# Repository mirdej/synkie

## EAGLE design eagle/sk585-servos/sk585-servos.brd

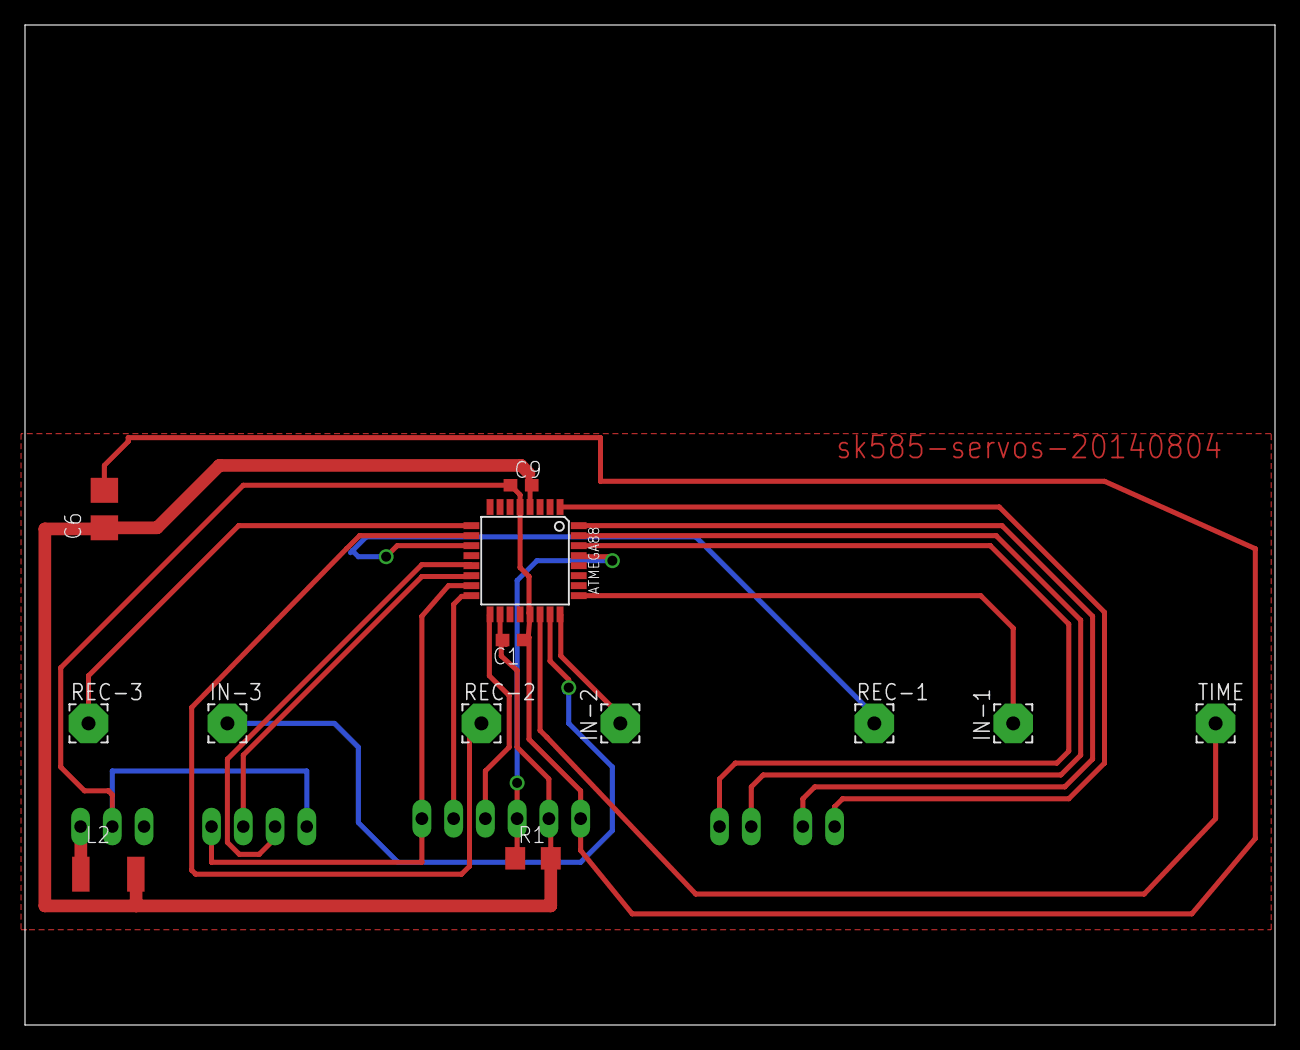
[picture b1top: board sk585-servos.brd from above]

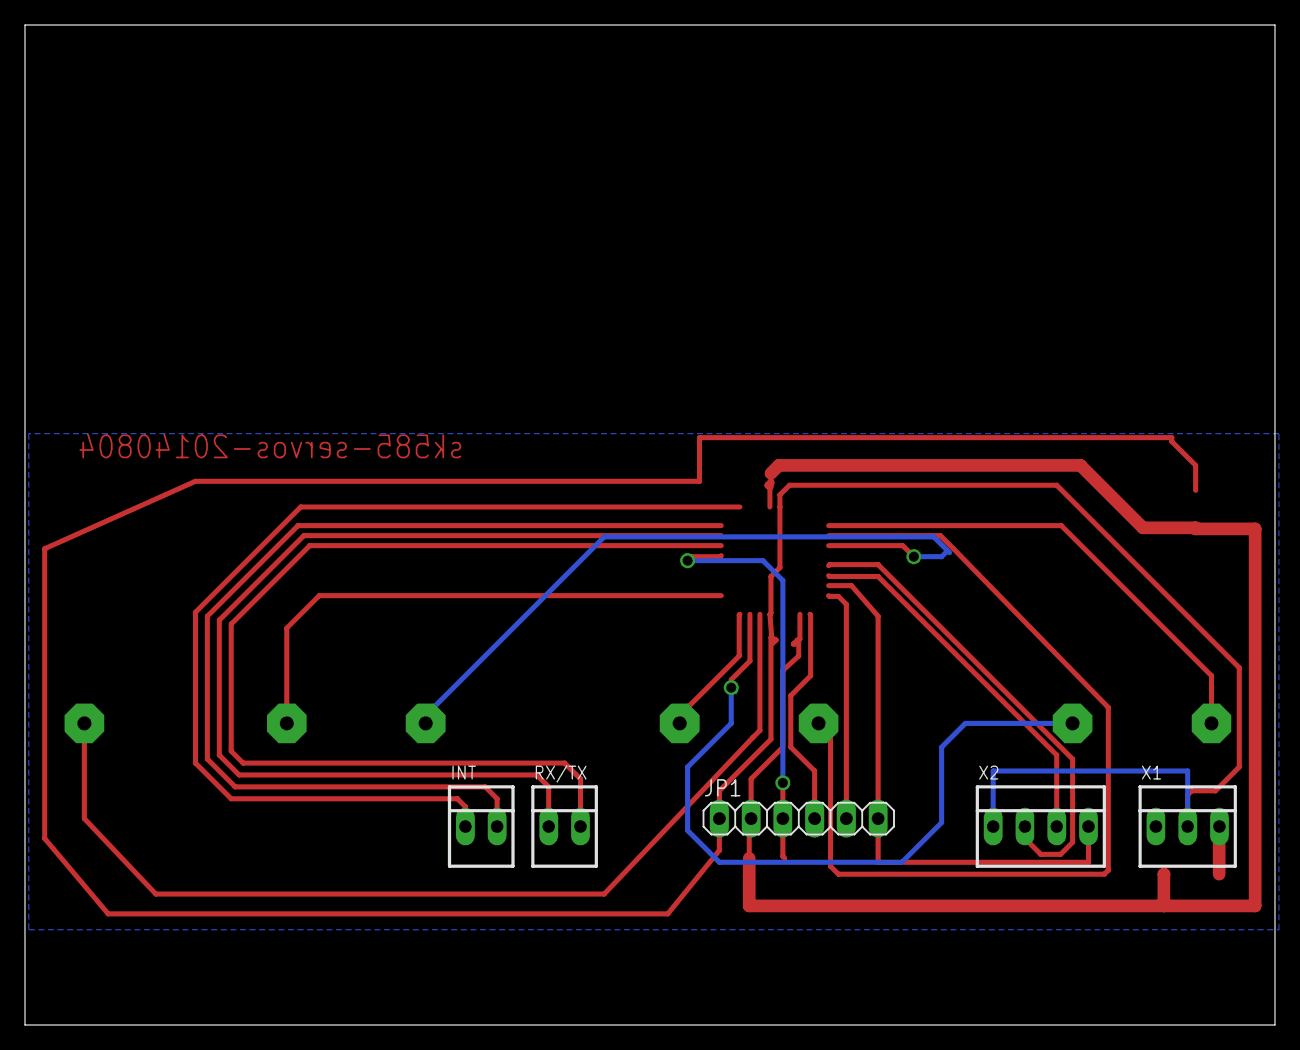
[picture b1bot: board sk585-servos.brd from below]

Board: 2 copper layers, 100.0 x 80.0 mm, 18 parts (5 on the bottom side), 20 nets.

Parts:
ATMEGA88: ATMEGA88; TQFP32-08
C1, C9: C0603
C6: 10u; CT3528
IN-1, IN-2, IN-3: 3,17/1,1
INT: 22-23-2021
JP1: 1X06
L2: L5038P
R1: R1206
REC-1, REC-2, REC-3: 3,17/1,1
RX/TX: 22-23-2021
TIME: 3,17/1,1
X1: 22-23-2031
X2: 22-23-2041

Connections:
+5V: ATMEGA88.4, ATMEGA88.18, C1.2, C6.+, C9.2, JP1.2, L2.2, R1.2
GND: ATMEGA88.5, ATMEGA88.21, C1.1, C6.-, C9.1, JP1.1, X1.2, X2.1
unnamed: ATMEGA88.29, JP1.3, R1.1
unnamed: ATMEGA88.17, JP1.4
unnamed: ATMEGA88.16, JP1.5
unnamed: ATMEGA88.23, IN-3.1
unnamed: ATMEGA88.24, IN-2.1
unnamed: ATMEGA88.25, IN-1.1
unnamed: ATMEGA88.22, TIME.1
unnamed: ATMEGA88.31, RX/TX.1
unnamed: ATMEGA88.11, REC-1.1
unnamed: ATMEGA88.10, REC-2.1
unnamed: L2.1, X1.3
unnamed: ATMEGA88.9, REC-3.1
unnamed: ATMEGA88.30, RX/TX.2
unnamed: ATMEGA88.1, INT.1
unnamed: ATMEGA88.13, X2.2
unnamed: ATMEGA88.32, INT.2
unnamed: ATMEGA88.14, X2.3
unnamed: ATMEGA88.15, JP1.6, X2.4

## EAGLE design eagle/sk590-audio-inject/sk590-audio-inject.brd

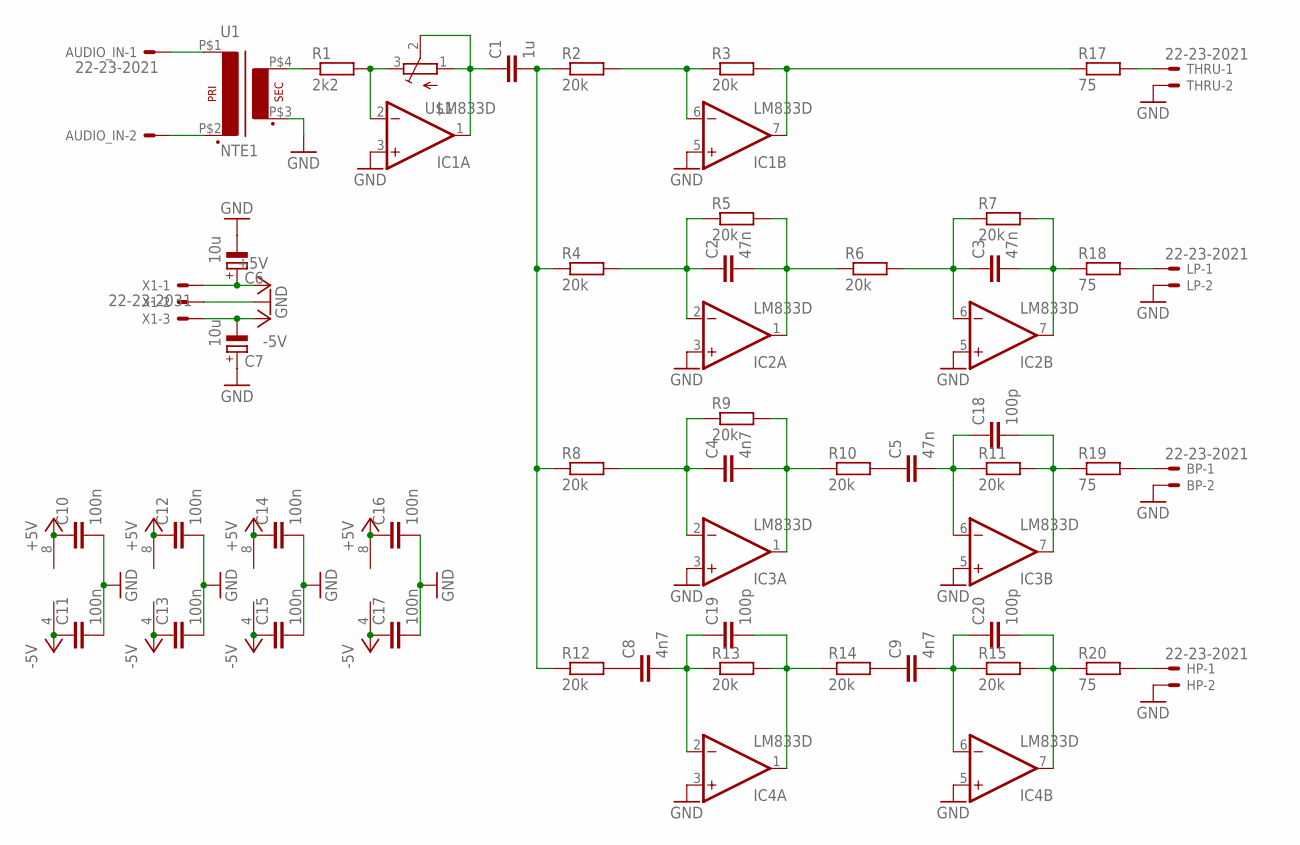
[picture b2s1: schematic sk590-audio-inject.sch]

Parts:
AUDIO_IN: 22-23-2021
BP: 22-23-2021
C1: 1u; C1206
C2, C3, C5: 47n; C1206
C4, C8, C9: 4n7; C1206
C6, C7: 10u; CT3528
C10, C11, C12, C13, C14, C15, C16, C17: 100n; C1206
C18, C19, C20: 100p; C1206
HP: 22-23-2021
IC1, IC2, IC3, IC4: LM833D; SO08
LP: 22-23-2021
R1: 2k2; R1206
R2, R3, R4, R5, R6, R7, R8, R9, R10, R11, R12, R13, R14, R15: 20k; R1206
R17, R18, R19, R20: 75; R1206
THRU: 22-23-2021
U1: NTE1; AUDIOTRAFO
U$1: ALPS_RK09K111_HOHNE-FüSSE; ALPS_RK09K111
X1: 22-23-2031

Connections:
+5V: C6.+, C10.1, C12.1, C14.1, C16.1, IC1.8 (V+), IC2.8 (V+), IC3.8 (V+), IC4.8 (V+), X1.1
-5V: C7.-, C11.1, C13.1, C15.1, C17.1, IC1.4 (V-), IC2.4 (V-), IC3.4 (V-), IC4.4 (V-), X1.3
GND: BP.2, C6.-, C7.+, C10.2, C11.2, C12.2, C13.2, C14.2, C15.2, C16.2, C17.2, HP.2, IC1.3 (+IN), IC1.5 (+IN), IC2.3 (+IN), IC2.5 (+IN), IC3.3 (+IN), IC3.5 (+IN), IC4.3 (+IN), IC4.5 (+IN), LP.2, THRU.2, U1.P$3 (S3), X1.2
unnamed: R1.1, U1.P$4 (S4)
unnamed: AUDIO_IN.1, U1.P$1 (P1)
unnamed: AUDIO_IN.2, U1.P$2 (P2)
unnamed: IC1.2 (-IN), R1.2, U$1.3 (E)
unnamed: C1.1, IC1.1 (OUT), U$1.1 (S), U$1.2 (W)
unnamed: C1.2, R2.1, R4.1, R8.1, R12.1
unnamed: IC1.6 (-IN), R2.2, R3.1
unnamed: IC1.7 (OUT), R3.2, R17.1
unnamed: C2.1, IC2.2 (-IN), R4.2, R5.1
unnamed: C2.2, IC2.1 (OUT), R5.2, R6.1
unnamed: C3.1, IC2.6 (-IN), R6.2, R7.1
unnamed: C3.2, IC2.7 (OUT), R7.2, R18.1
unnamed: C5.1, R10.2
unnamed: C8.1, R12.2
unnamed: C4.1, IC3.2 (-IN), R8.2, R9.1
unnamed: C8.2, C19.1, IC4.2 (-IN), R13.1
unnamed: C19.2, IC4.1 (OUT), R13.2, R14.1
unnamed: C4.2, IC3.1 (OUT), R9.2, R10.1
unnamed: C5.2, C18.1, IC3.6 (-IN), R11.1
unnamed: C18.2, IC3.7 (OUT), R11.2, R19.1
unnamed: C9.1, R14.2
unnamed: C9.2, C20.1, IC4.6 (-IN), R15.1
unnamed: C20.2, IC4.7 (OUT), R15.2, R20.1
unnamed: R17.2, THRU.1
unnamed: LP.1, R18.2
unnamed: BP.1, R19.2
unnamed: HP.1, R20.2

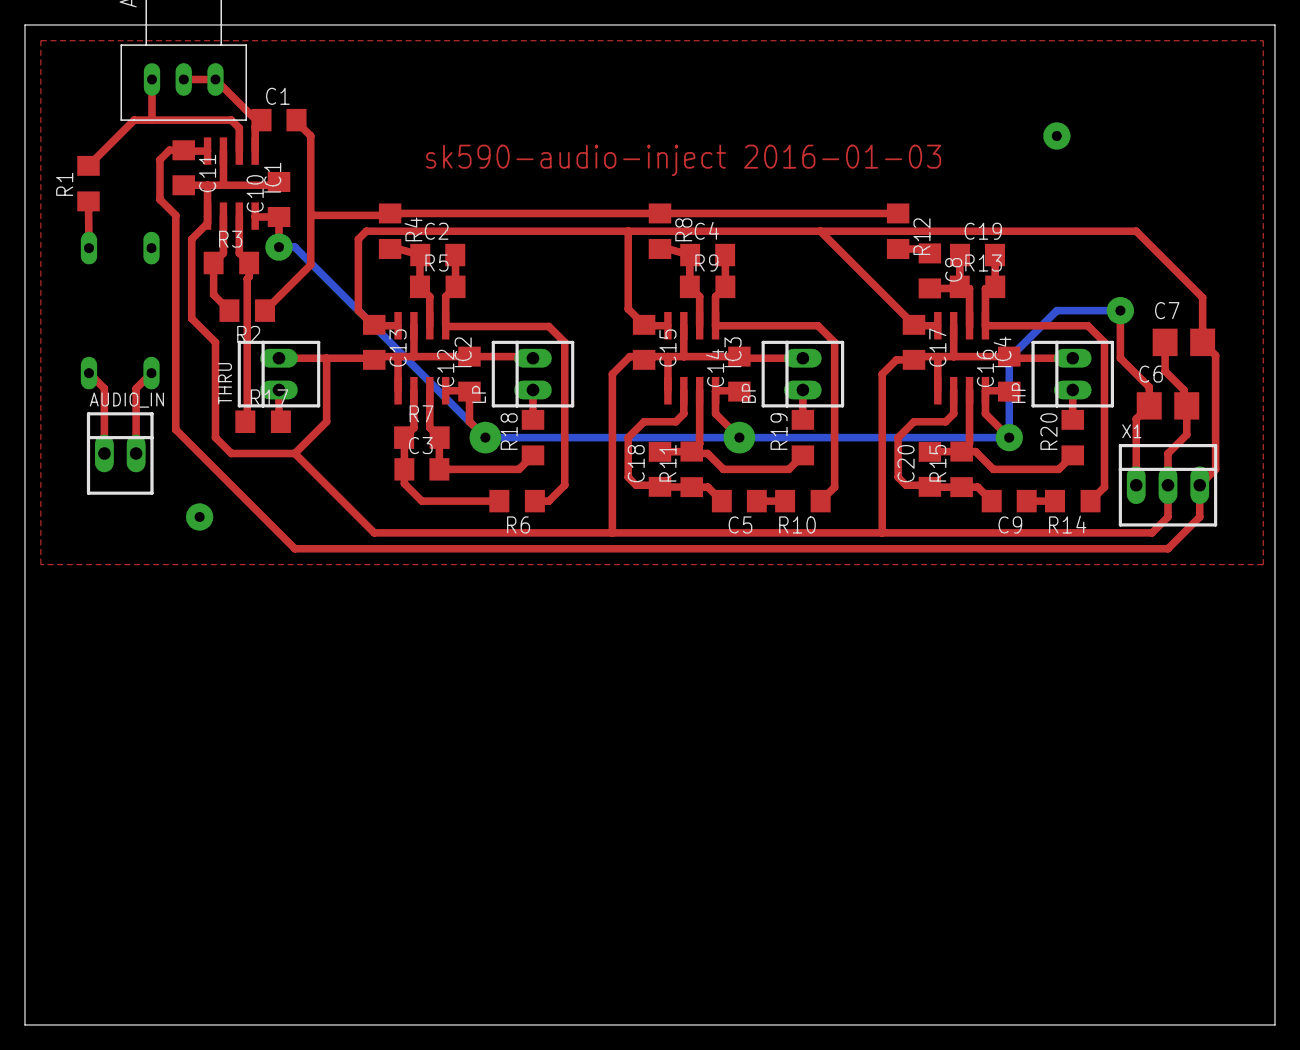
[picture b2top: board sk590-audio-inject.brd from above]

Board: 2 copper layers, 100.0 x 80.0 mm, 51 parts (0 on the bottom side), 30 nets.

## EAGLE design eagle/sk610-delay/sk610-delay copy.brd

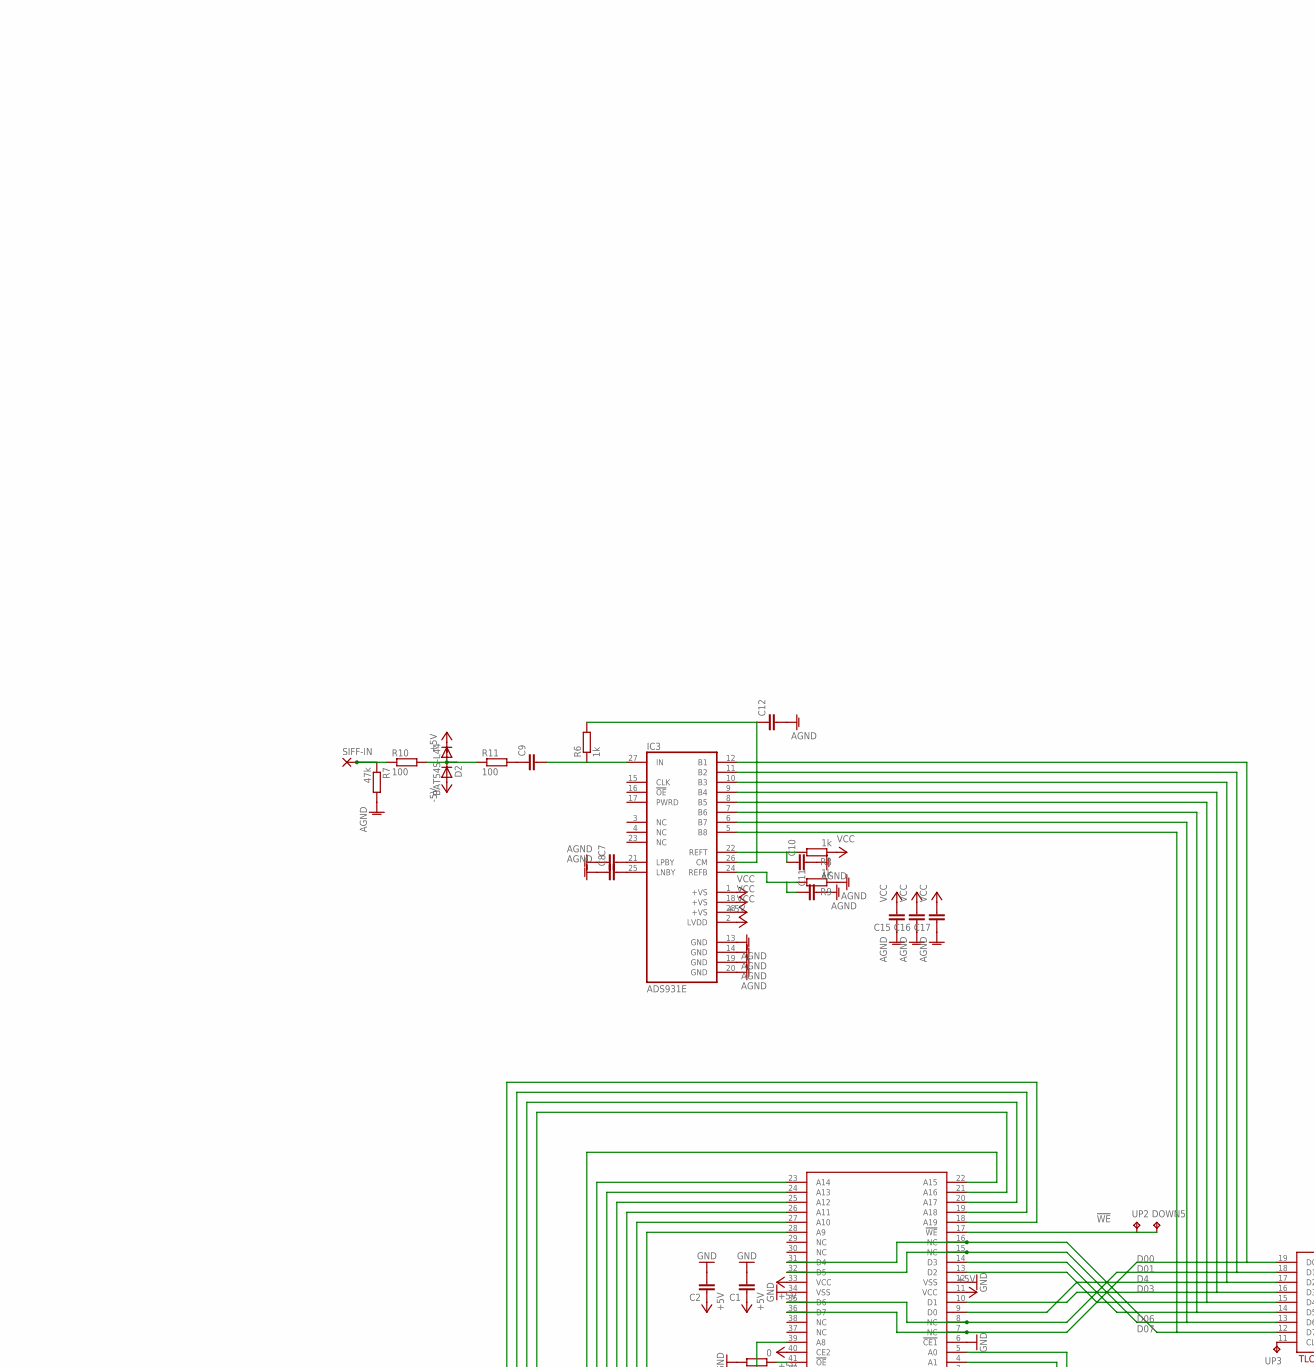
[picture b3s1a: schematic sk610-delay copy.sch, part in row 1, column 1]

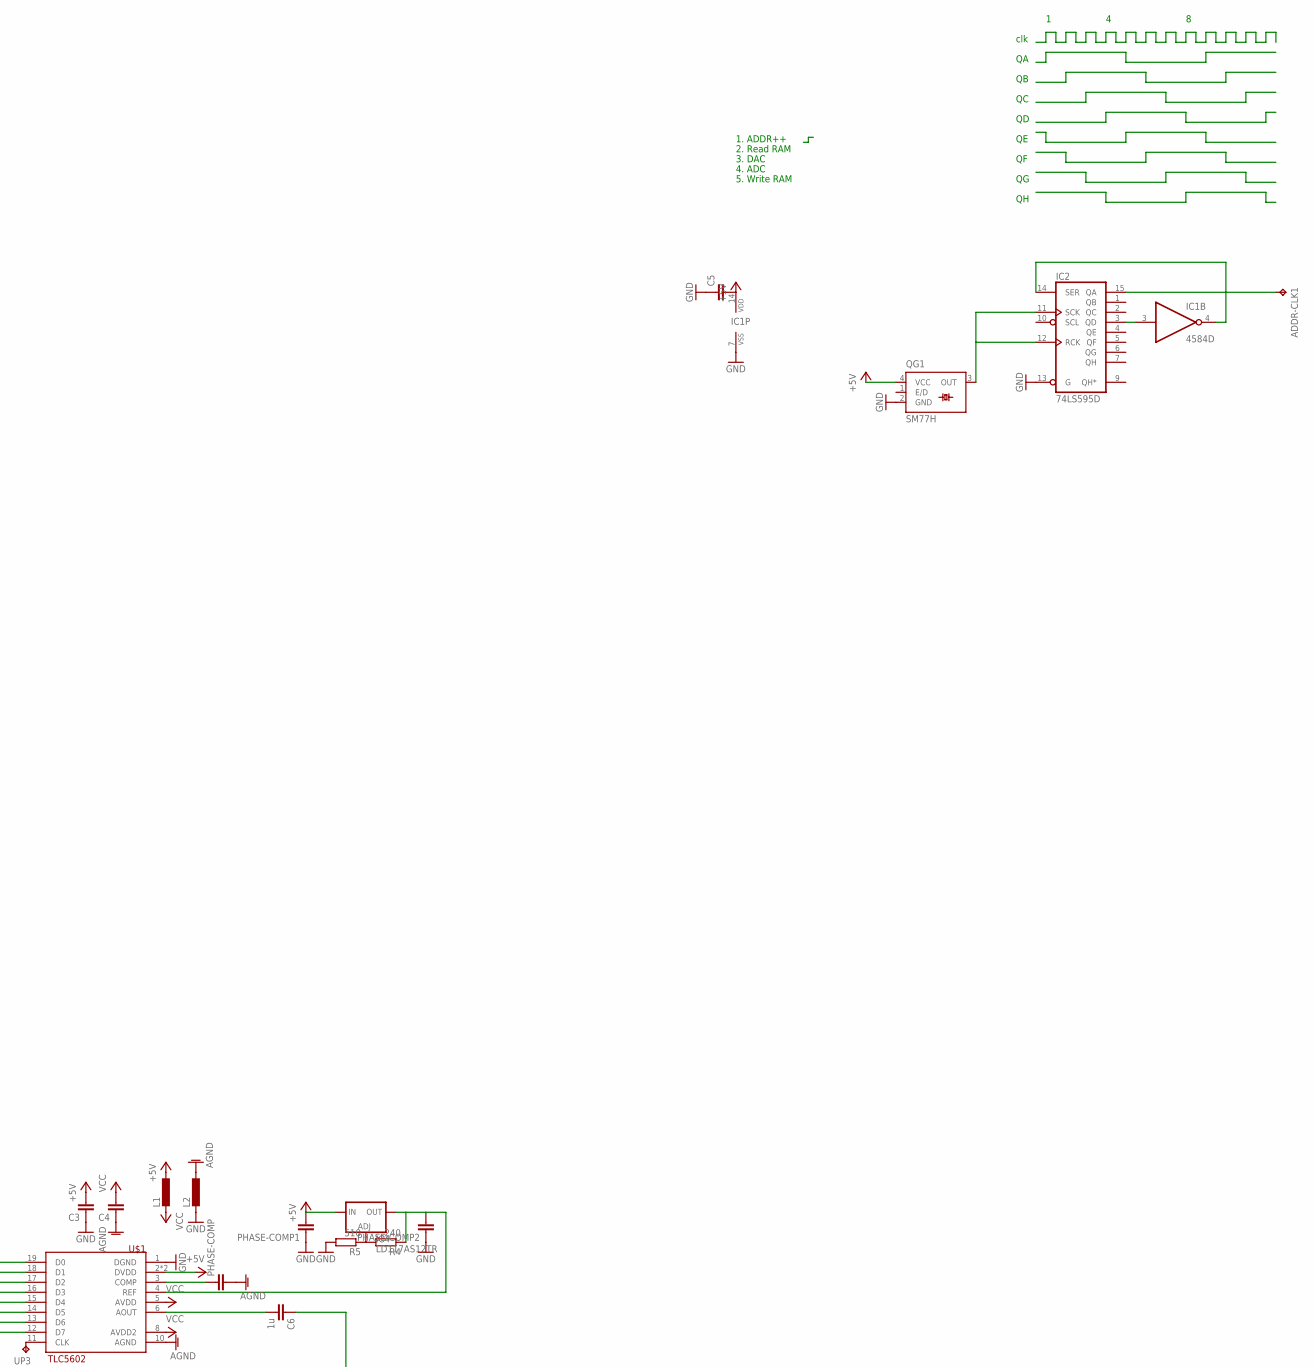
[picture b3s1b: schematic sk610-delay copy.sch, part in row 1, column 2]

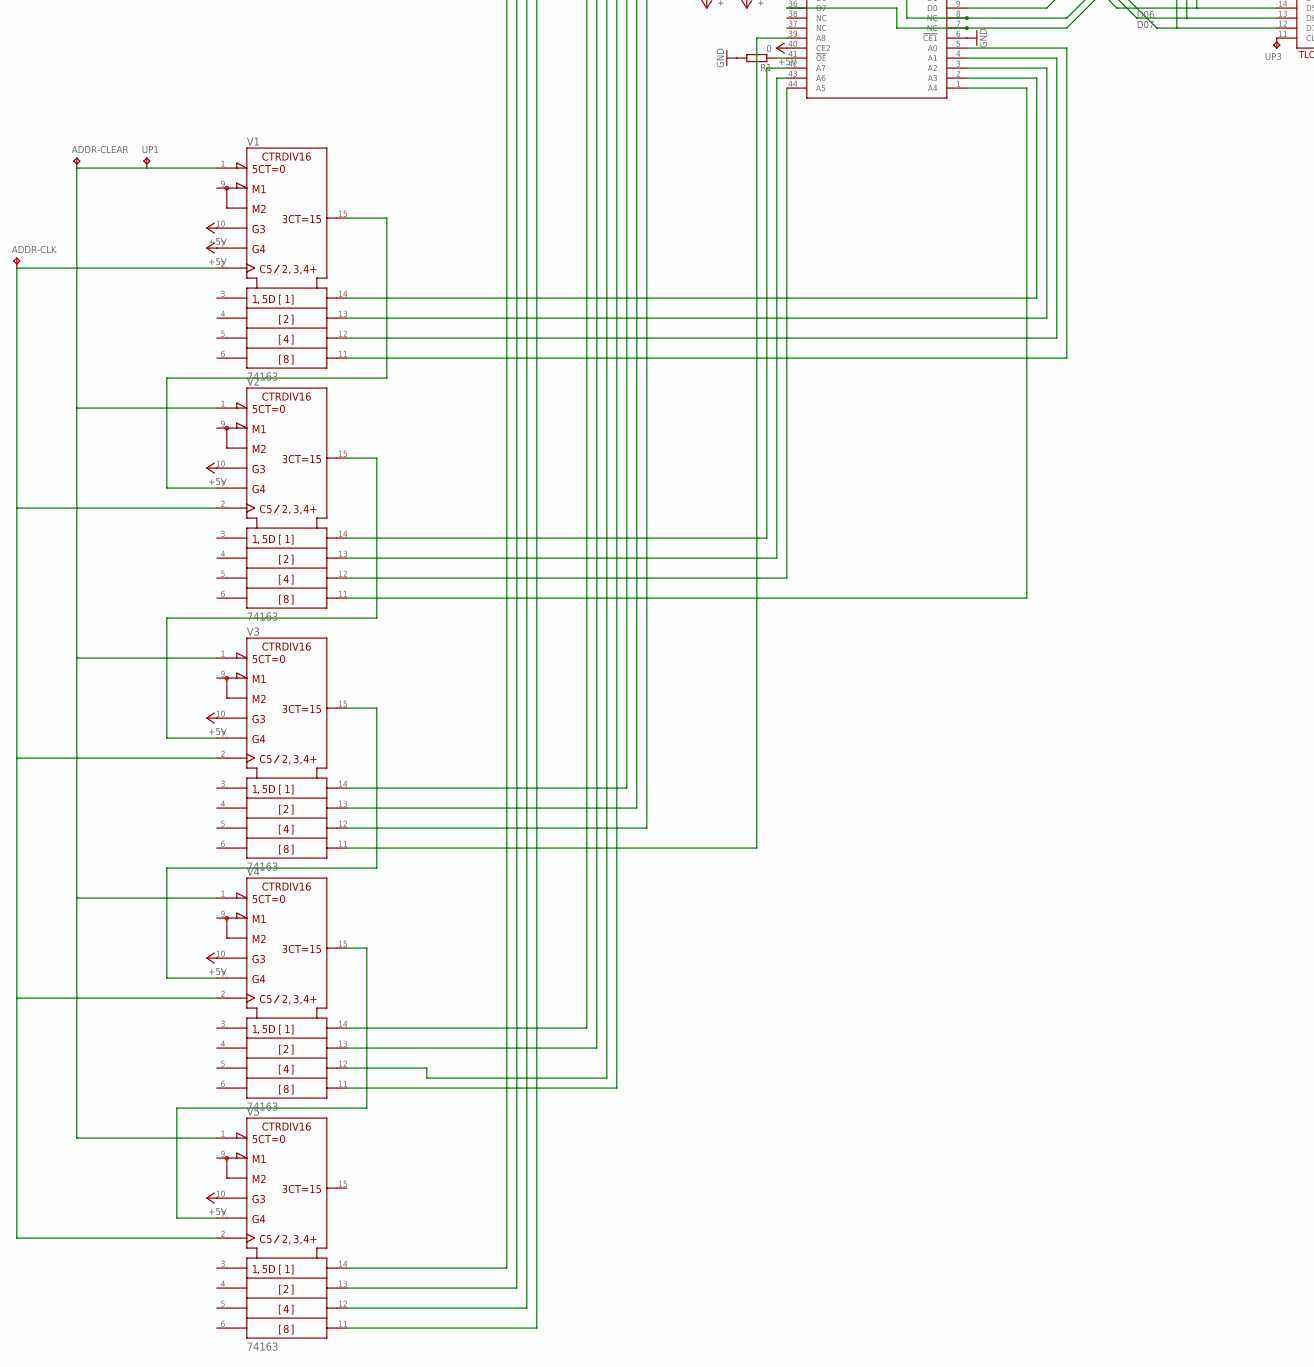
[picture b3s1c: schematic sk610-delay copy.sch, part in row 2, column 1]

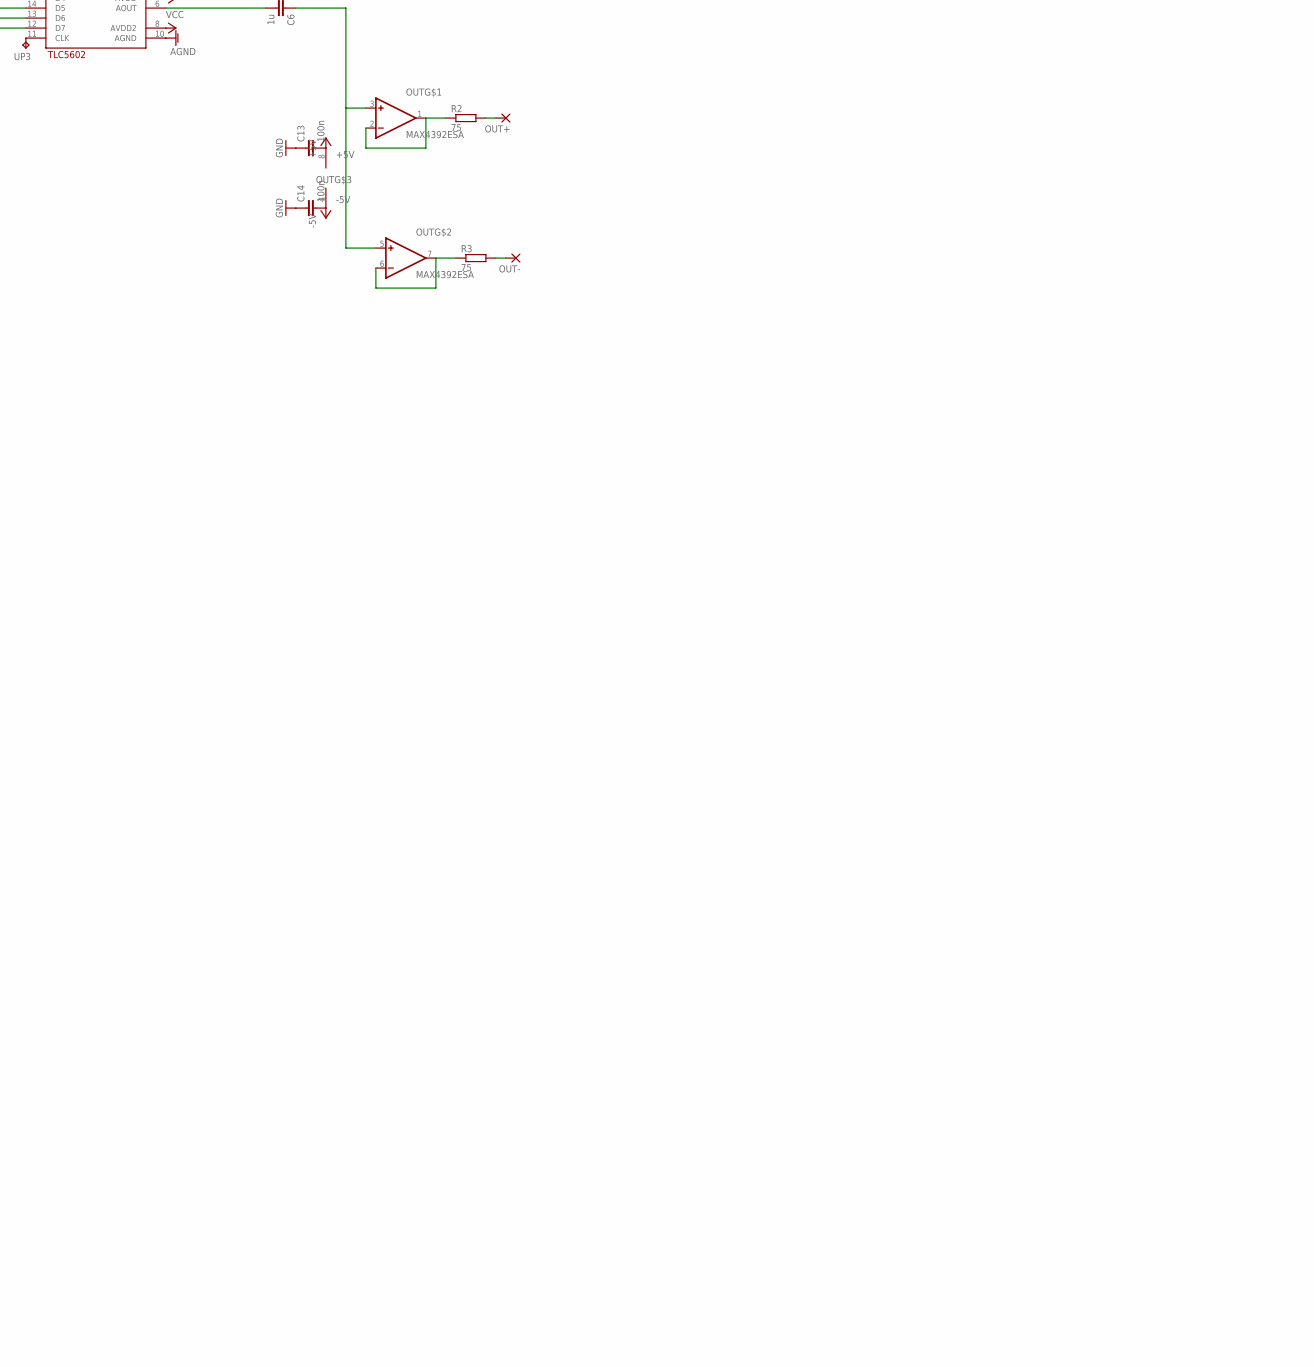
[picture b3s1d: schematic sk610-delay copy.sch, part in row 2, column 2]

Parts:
ADDR-CLEAR: TPTP14R; TP14R
ADDR-CLK, ADDR-CLK1: TPTP14R; TP14R
C1, C2, C7, C8, C10, C11, C12, C15, C16, C17: C-EUC0603; C0603
C3, C4, C5, C9: C-EUC1206; C1206
C6: 1u; C1206
C13, C14: 100n; C0805
D2: BAT54S-L44; SOT23
DOWN5: TPTP14R; TP14R
IC1: 4584D; SO14
IC2: 74LS595D; SO16
IC3: ADS931E; SSOP28BU
IC4: LD117AS12TR; SOT223
L1, L2: L-EUL1812; L1812
OUT: MAX4392ESA; SO08
OUT+: 3,17/1,1
OUT-: 3,17/1,1
PHASE-COMP, PHASE-COMP1, PHASE-COMP2: C-EUC1206; C1206
QG1: SM77H
R1: 0; R1206
R2, R3: 75; R1206
R4: 240; R1206
R5: 510; R1206
R6, R8, R9: 1k; R1206
R7: 47k; R1206
R10, R11: 100; R1206
SIFF-IN: 3,17/1,1
U$1: TLC5602; SO20W
U$2: CY62158E; TSOPII-Z44
UP1, UP2, UP3: TPTP14R; TP14R
V1, V2, V3, V4, V5: 74163; SO16

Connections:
!WE: DOWN5.TP, U$2.17 (!WE), UP2.TP
+5V: C1.1, C2.1, C3.2, C5.2, C13.2, D2.2 (C), IC1.14 (VDD), IC3.2 (LVDD), IC4.3 (IN), L1.1, OUT.8 (+5V), PHASE-COMP1.2, QG1.4 (VCC), U$1.2 (DVDD), U$1.9 (DVDD), U$2.11 (VCC), U$2.33 (VCC), U$2.40 (CE2), V1.7 (ENP), V1.10 (ENT), V2.10 (ENT), V3.10 (ENT), V4.10 (ENT), V5.10 (ENT)
+UB: V1.16 (+UB), V2.16 (+UB), V3.16 (+UB), V4.16 (+UB), V5.16 (+UB)
-5V: C14.2, D2.1 (A), OUT.4 (-5V)
-UB: V1.8 (-UB), V2.8 (-UB), V3.8 (-UB), V4.8 (-UB), V5.8 (-UB)
AGND: C4.1, C7.1, C8.1, C10.2, C11.2, C12.2, C15.1, C16.1, C17.1, IC3.13 (GND), IC3.14 (GND), IC3.19 (GND), IC3.20 (GND), L2.1, PHASE-COMP.2, R7.2, R9.1, U$1.10 (AGND)
D00: IC3.12 (B1), U$1.19 (D0), U$2.7 (NC), U$2.36 (D7)
D01: IC3.11 (B2), U$1.18 (D1), U$2.8 (NC), U$2.35 (D6)
D03: IC3.9 (B4), U$1.16 (D3), U$2.10 (D1)
D4: IC3.10 (B3), U$1.17 (D2), U$2.9 (D0)
D04: IC3.8 (B5), U$1.15 (D4), U$2.13 (D2)
D05: IC3.7 (B6), U$1.14 (D5), U$2.14 (D3)
D06: IC3.6 (B7), U$1.13 (D6), U$2.15 (NC), U$2.32 (D5)
D07: IC3.5 (B8), U$1.12 (D7), U$2.16 (NC), U$2.31 (D4)
GND: C1.2, C2.2, C3.1, C5.1, C13.1, C14.1, IC1.7 (VSS), IC2.8 (GND), IC2.13 (G), L2.2, PHASE-COMP1.1, PHASE-COMP2.1, QG1.2 (GND), R1.2, R5.2, U$1.1 (DGND), U$2.6 (!CE1), U$2.12 (VSS), U$2.34 (VSS)
unnamed: IC2.11 (SCK), IC2.12 (RCK), QG1.3 (OUT)
unnamed: IC1.3 (I), IC2.3 (QD)
unnamed: IC1.4 (O), IC2.14 (SER)
unnamed: C9.1, R11.2
unnamed: R7.1, R10.1, SIFF-IN.1
unnamed: D2.3 (AC), R10.2, R11.1
unnamed: U$2.2 (A3), V1.14 (QA)
unnamed: U$2.3 (A2), V1.13 (QB)
unnamed: U$2.4 (A1), V1.12 (QC)
unnamed: U$2.5 (A0), V1.11 (QD)
unnamed: ADDR-CLEAR.TP, UP1.TP, V1.1 (!CLR), V2.1 (!CLR), V3.1 (!CLR), V4.1 (!CLR), V5.1 (!CLR)
unnamed: U$2.1 (A4), V2.11 (QD)
unnamed: U$2.44 (A5), V2.12 (QC)
unnamed: U$2.43 (A6), V2.13 (QB)
unnamed: U$2.42 (A7), V2.14 (QA)
unnamed: V3.15 (RCO), V4.7 (ENP)
unnamed: V1.15 (RCO), V2.7 (ENP)
unnamed: V2.15 (RCO), V3.7 (ENP)
unnamed: U$2.39 (A8), V3.11 (QD)
unnamed: U$2.28 (A9), V3.12 (QC)
unnamed: U$2.27 (A10), V3.13 (QB)
unnamed: U$2.26 (A11), V3.14 (QA)
unnamed: U$2.25 (A12), V4.11 (QD)
unnamed: U$2.24 (A13), V4.12 (QC)
unnamed: R1.1, U$2.41 (!OE)
unnamed: U$2.23 (A14), V4.13 (QB)
unnamed: U$2.22 (A15), V4.14 (QA)
unnamed: U$2.21 (A16), V5.11 (QD)
unnamed: U$2.20 (A17), V5.12 (QC)
unnamed: U$2.19 (A18), V5.13 (QB)
unnamed: U$2.18 (A19), V5.14 (QA)
unnamed: ADDR-CLK.TP, V1.2 (CLK), V2.2 (CLK), V3.2 (CLK), V4.2 (CLK), V5.2 (CLK)
unnamed: ADDR-CLK1.TP, IC2.15 (QA)
unnamed: V4.15 (RCO), V5.7 (ENP)
unnamed: PHASE-COMP.1, U$1.3 (COMP)
unnamed: C6.2, U$1.6 (AOUT)
unnamed: OUT+.1, R2.2
unnamed: C6.1, OUT.3 (+IN), OUT.5 (+IN)
unnamed: OUT-.1, R3.2
unnamed: U$1.11 (CLK), UP3.TP
unnamed: OUT.1 (OUT), OUT.2 (-IN), R2.1
unnamed: OUT.6 (-IN), OUT.7 (OUT), R3.1
unnamed: IC4.4 (OUT), PHASE-COMP2.2, R4.1, U$1.4 (REF)
unnamed: IC4.1 (ADJ), R4.2, R5.1
unnamed: C7.2, IC3.21 (LPBY)
unnamed: C8.2, IC3.25 (LNBY)
unnamed: C9.2, IC3.27 (IN), R6.1
unnamed: C12.1, IC3.26 (CM), R6.2
unnamed: C10.1, IC3.22 (REFT), R8.2
unnamed: C11.1, IC3.24 (REFB), R9.2
VCC: C4.2, C15.2, C16.2, C17.2, IC2.16 (VCC), IC3.1 (+VS), IC3.18 (+VS), IC3.28 (+VS), L1.2, R8.1, U$1.5 (AVDD), U$1.8 (AVDD2)

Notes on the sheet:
clk
1. ADDR++
2. Read RAM
3. DAC
4. ADC
5. Write RAM

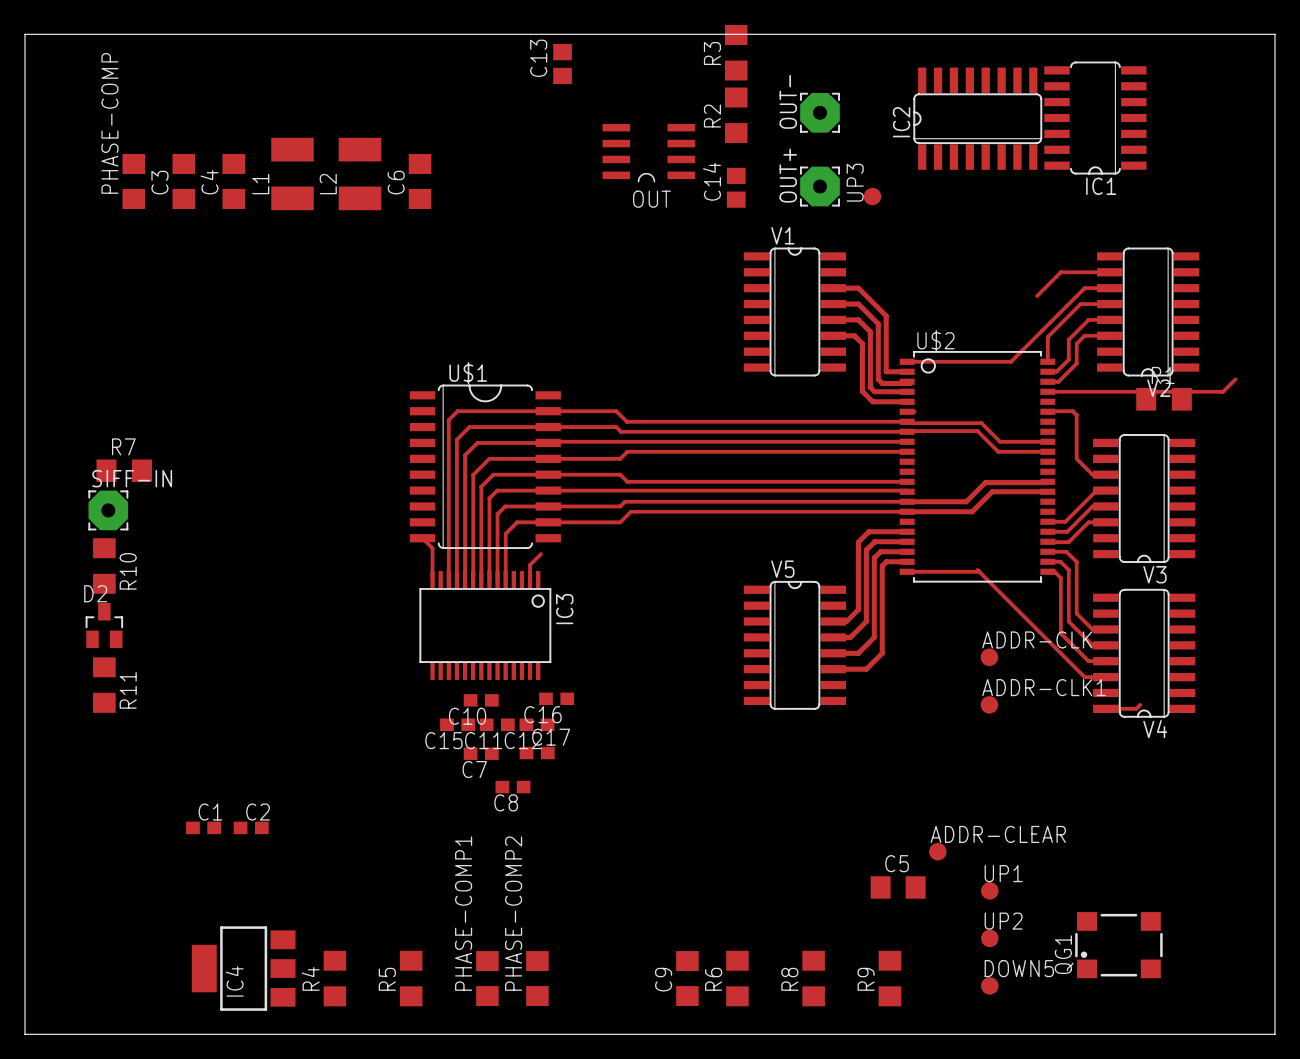
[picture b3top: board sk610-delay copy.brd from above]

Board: 2 copper layers, 100.0 x 80.0 mm, 57 parts (0 on the bottom side), 66 nets.

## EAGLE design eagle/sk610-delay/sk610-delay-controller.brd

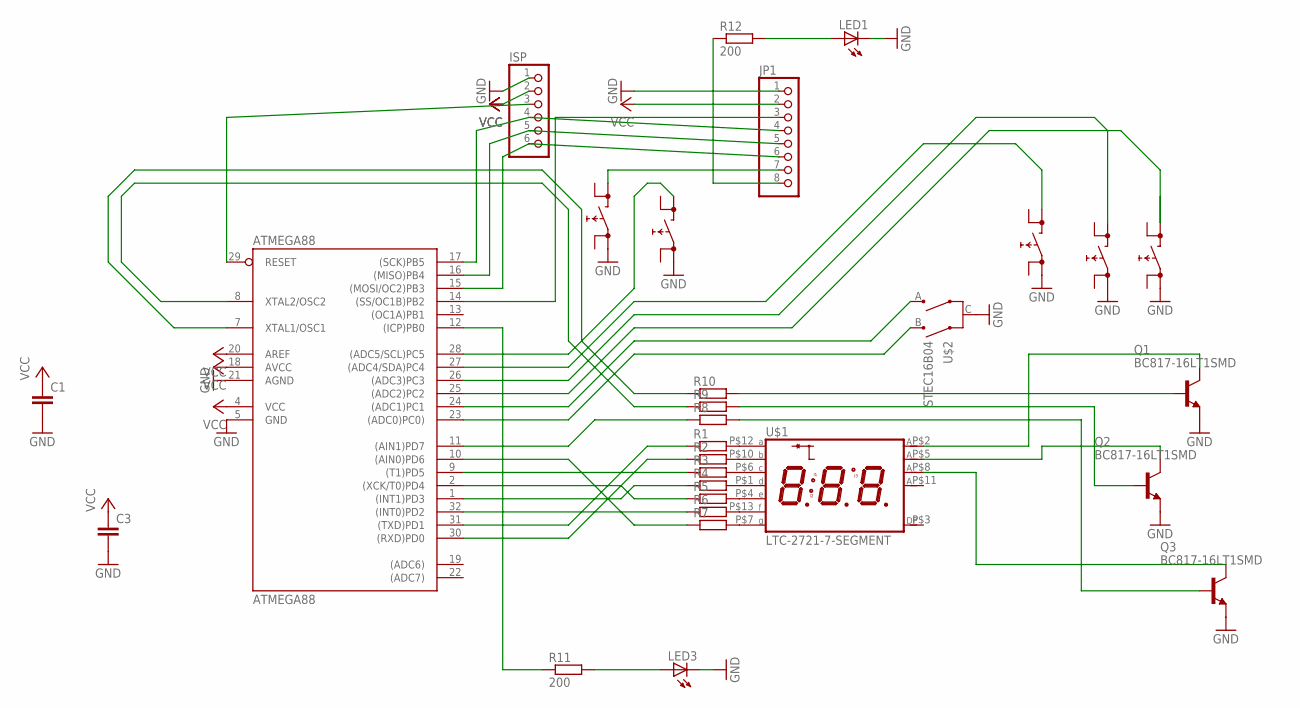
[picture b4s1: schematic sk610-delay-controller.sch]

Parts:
ATMEGA88: ATMEGA88; TQFP32-08
C1, C3: C-EUC0603; C0603
ISP: PINHD-1X6; 1X06
JP1: PINHD-1X8; 1X08
LED1, LED3: LEDCHIPLED_1206; CHIPLED_1206
LOOPER: PRINTTASTER_SMD; SMD_SWITCH
Q1, Q2, Q3: BC817-16LT1SMD; SOT23-BEC
R1, R2, R3, R4, R5, R6, R7, R8, R9, R10: R-EU_R1206; R1206
R11, R12: 200; R1206
REC: PRINTTASTER_SMD; SMD_SWITCH
U$1: LTC-2721-7-SEGMENT; LTC-2721
U$2: STEC16B04
U$3, U$4, U$5: PRINTTASTER_SMD; SMD_SWITCH

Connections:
GND: ATMEGA88.5 (GND), ATMEGA88.21 (AGND), C1.2, C3.2, ISP.1, JP1.1, LED1.C, LED3.C, LOOPER.AA (0), Q1.E, Q2.E, Q3.E, REC.AA (0), U$2.C, U$3.AA (0), U$4.AA (0), U$5.AA (0); also elsewhere on the board
MISO: ATMEGA88.16 ((MISO)PB4), ISP.5, JP1.5; also elsewhere on the board
MOSI: ATMEGA88.15 ((MOSI/OC2)PB3), ISP.6, JP1.6; also elsewhere on the board
unnamed: ATMEGA88.30 ((RXD)PD0), R2.1
unnamed: ATMEGA88.31 ((TXD)PD1), R1.1
unnamed: ATMEGA88.32 ((INT0)PD2), R6.1
unnamed: ATMEGA88.1 ((INT1)PD3), R4.1
unnamed: ATMEGA88.2 ((XCK/T0)PD4), R5.1
unnamed: ATMEGA88.8 (XTAL2/OSC2), R9.1
unnamed: ATMEGA88.7 (XTAL1/OSC1), R10.1
unnamed: ATMEGA88.11 ((AIN1)PD7), R8.1
unnamed: ATMEGA88.9 ((T1)PD5), R3.1
unnamed: R1.2, U$1.P$12 (A)
unnamed: R2.2, U$1.P$10 (B)
unnamed: R3.2, U$1.P$6 (C)
unnamed: R4.2, U$1.P$1 (D)
unnamed: R5.2, U$1.P$4 (E)
unnamed: R6.2, U$1.P$13 (F)
unnamed: R7.2, U$1.P$7 (G)
unnamed: ATMEGA88.29 (RESET), ISP.3
unnamed 20: ATMEGA88.13 ((OC1A)PB1); also elsewhere on the board
unnamed: ATMEGA88.10 ((AIN0)PD6), R7.1
unnamed: ATMEGA88.23 ((ADC0)PC0)), U$2.B
unnamed: ATMEGA88.24 ((ADC1)PC1), U$2.A
unnamed: Q1.B, R10.2
unnamed: Q2.B, R9.2
unnamed: Q3.B, R8.2
unnamed: Q1.C, U$1.P$2 (D1)
unnamed: Q2.C, U$1.P$5 (D2)
unnamed: Q3.C, U$1.P$8 (D3)
unnamed: ATMEGA88.25 ((ADC2)PC2), U$5.BB (1)
unnamed: ATMEGA88.26 ((ADC3)PC3), U$3.BB (1)
unnamed: ATMEGA88.27 ((ADC4/SDA)PC4), U$4.BB (1)
unnamed 33: JP1.7, REC.BB (1); also elsewhere on the board
unnamed: ATMEGA88.28 ((ADC5/SCL)PC5), LOOPER.BB (1)
unnamed: ATMEGA88.12 ((ICP)PB0), R11.1
unnamed: LED1.A, R12.2
unnamed 37: JP1.8, R12.1; also elsewhere on the board
unnamed: LED3.A, R11.2
SCK: ATMEGA88.17 ((SCK)PB5), ISP.4, JP1.4; also elsewhere on the board
SS: ATMEGA88.14 ((SS/OC1B)PB2), JP1.3; also elsewhere on the board
VCC: ATMEGA88.4 (VCC), ATMEGA88.18 (AVCC), ATMEGA88.20 (AREF), C1.1, C3.1, ISP.2, JP1.2; also elsewhere on the board

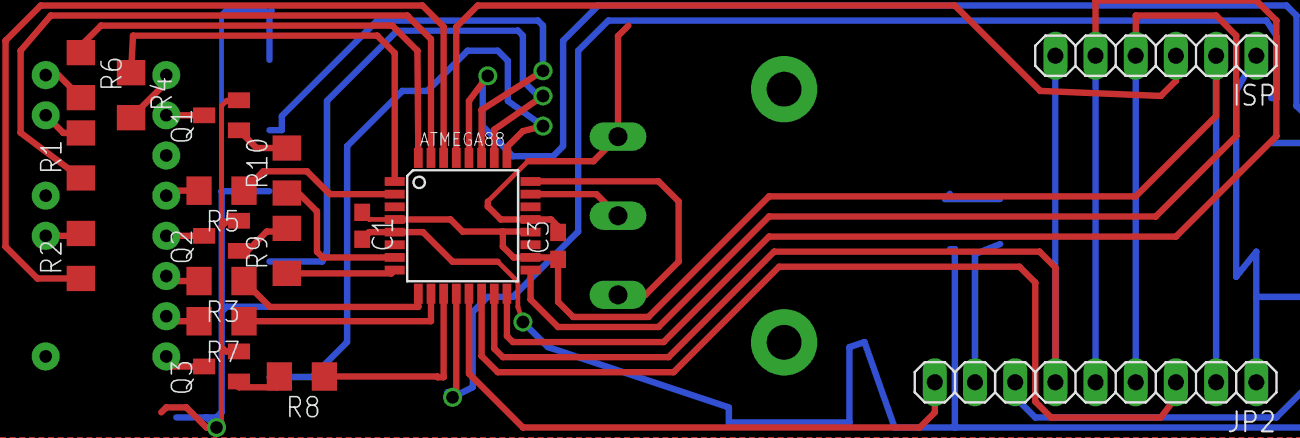
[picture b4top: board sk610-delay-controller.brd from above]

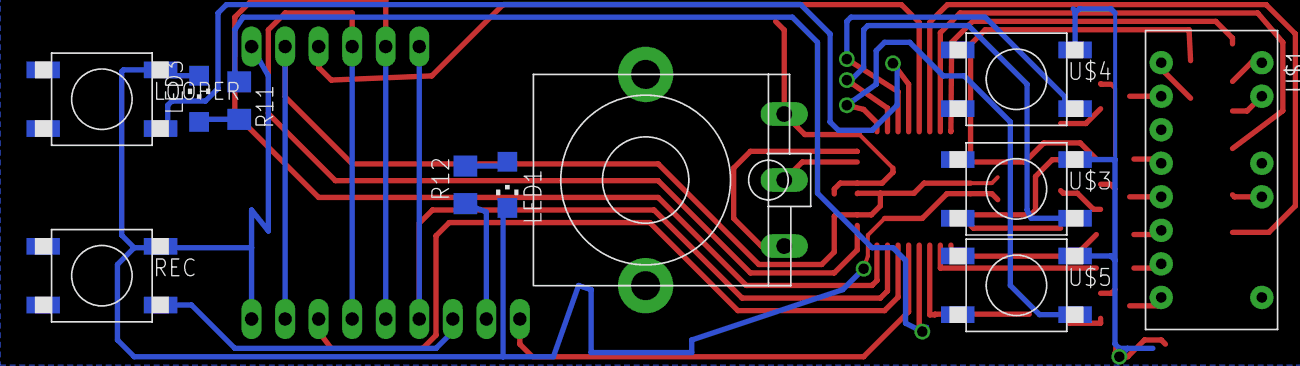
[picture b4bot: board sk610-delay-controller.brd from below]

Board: 2 copper layers, 29 parts (11 on the bottom side), 42 nets.

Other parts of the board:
JP2: 1X09

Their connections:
GND: JP2.1; also elsewhere on the board
MISO: JP2.5; also elsewhere on the board
MOSI: JP2.6; also elsewhere on the board
unnamed 20: JP2.9; also elsewhere on the board
unnamed 33: JP2.7; also elsewhere on the board
unnamed 37: JP2.8; also elsewhere on the board
SCK: JP2.4; also elsewhere on the board
SS: JP2.3; also elsewhere on the board
VCC: JP2.2; also elsewhere on the board
